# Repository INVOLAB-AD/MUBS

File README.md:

# MUBS_Drone_Design

It is the schematic design of the small microcontroller chip and of MUBS drones

The main components of the chip are:
1. ATTINY85U
2. MALE USB PORT
3. LEDS
4. RESISTORS
5. DIODES IN14007
6. PIN HEADERS

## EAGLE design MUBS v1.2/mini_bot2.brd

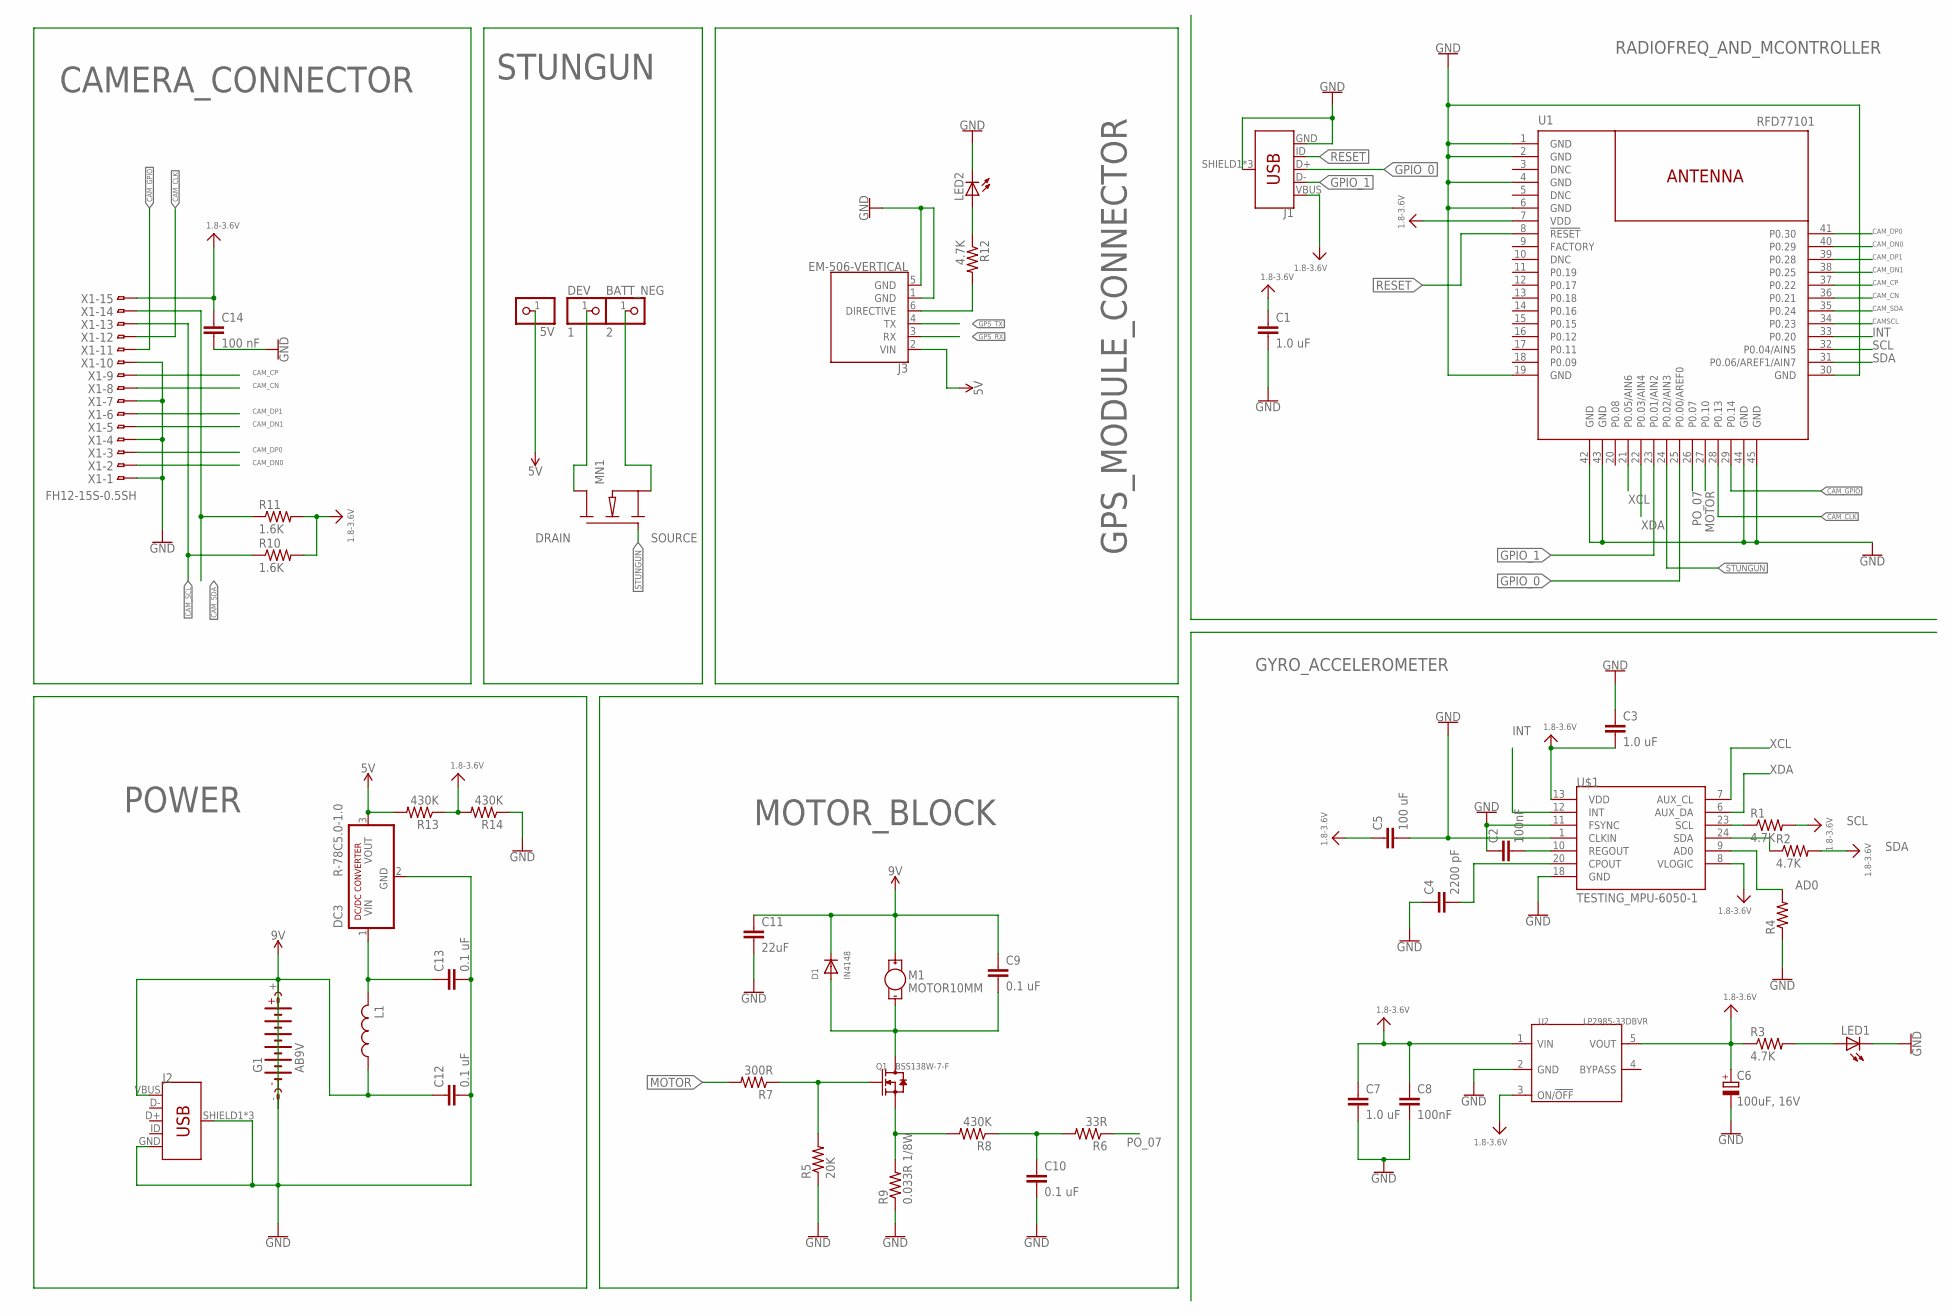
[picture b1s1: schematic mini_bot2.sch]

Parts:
5V: PINHD-1X1; 1X01
BATT_NEG: 2; 1X01
C1, C3, C7: 1.0 uF; C2.5-3
C2, C8: 100nF; C2.5-3
C4: 2200 pF; C2.5-3
C5: 100 uF; C2.5-3
C6: 100uF, 16V; A/3216-18R
C9, C10, C12, C13: 0.1 uF; C2.5-3
C11: 22uF; C2.5-3
C14: 100 nF; C2.5-3
D1: IN4148; DO-1N4148
DC3: R-78C5.0-1.0; SIP3
DEV: 1; 1X01
G1: AB9V
J1, J2: USB_MICRO-BREDUCED_PASTE; USB-B-MICRO-SMD_RED_PASTE
J3: EM-506-VERTICAL; JST-6PIN-1MM
L1: L-USL1812; L1812
LED1, LED2: LEDCHIPLED_1206; CHIPLED_1206
M1: MOTOR10MM; VIBE-MOTOR-10MM
MN1: NMOS; SOT23
Q1: BSS138W-7-F; SOT-23
R1, R2, R3, R12: 4.7K; M0805
R4: R-US_M0805; M0805
R5: 20K; M0805
R6: 33R; M0805
R7: 300R; M0805
R8, R13, R14: 430K; M0805
R9: 0.033R 1/8W; M0805
R10, R11: 1.6K; M0805
U1: RFD77101
U2: LP2985-33DBVR; SOT-23-5
U$1: TESTING_MPU-6050-1; TESTING_QFN-24-4MM2
X1: FH12-15S-0.5SH

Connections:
5V: 5V.1, DC3.3 (VOUT), J3.2 (VIN), R13.2
12V: C9.1, C11.1, C12.1, D1.C, G1.+, J2.VBUS, L1.1, M1.+
AD0: R4.2, U$1.9 (AD0)
CAMSCL: U1.34 (P0.23)
CAM_CLK: U1.28 (P0.13), X1.12
CAM_CN: U1.36 (P0.21), X1.8
CAM_CP: U1.37 (P0.22), X1.9
CAM_DN0: U1.40 (P0.29), X1.2
CAM_DN1: U1.38 (P0.25), X1.5
CAM_DP0: U1.41 (P0.30), X1.3
CAM_DP1: U1.39 (P0.28), X1.6
CAM_GPIO: U1.29 (P0.14), X1.11
CAM_SCL: R10.1, X1.13
CAM_SDA: R11.1, U1.35 (P0.24), X1.14
DRAIN: DEV.1, MN1.3 (D)
GND: C1.2, C2.1, C3.1, C4.1, C5.2, C6.-, C7.2, C8.2, C10.2, C11.2, C12.2, C13.2, C14.2, DC3.2 (GND), G1.-, J1.GND, J1.SHIELD1 (SHIELD), J1.SHIELD2 (SHIELD), J1.SHIELD3 (SHIELD), J2.GND, J2.SHIELD1 (SHIELD), J2.SHIELD2 (SHIELD), J2.SHIELD3 (SHIELD), J3.1 (GND), J3.5 (GND), LED1.C, LED2.C, R4.1, R5.1, R9.1, R14.1, U1.1 (GND), U1.2 (GND), U1.4 (GND), U1.6 (GND), U1.19 (GND), U1.30 (GND), U1.42 (GND), U1.43 (GND), U1.44 (GND), U1.45 (GND), U2.2 (GND), U$1.1 (CLKIN), U$1.11 (FSYNC), U$1.18 (GND), X1.1, X1.4, X1.7, X1.10
GPIO_0: J1.D+, U1.25 (P0.00/AREF0)
GPIO_1: J1.D-, U1.23 (P0.01/AIN2)
GPS_RX: J3.3 (RX)
GPS_TX: J3.4 (TX)
INT: U1.33 (P0.20), U$1.12 (INT)
MOTOR: R7.2, U1.27 (P0.10)
unnamed: C9.2, D1.A, M1.-, Q1.3 (D)
unnamed: LED1.A, R3.2
unnamed: C4.2, U$1.20 (CPOUT)
unnamed: C2.2, U$1.10 (REGOUT)
unnamed: C13.1, DC3.1 (VIN), L1.2
unnamed: Q1.2 (S), R8.2, R9.2
unnamed: C10.1, R6.2, R8.1
unnamed: Q1.1 (G), R5.2, R7.1
unnamed: J3.6 (DIRECTIVE), R12.2
unnamed: LED2.A, R12.1
PO_07: R6.1, U1.26 (P0.07)
RESET: J1.ID, U1.8 (!RESET!)
SCL: R1.1, U1.32 (P0.04/AIN5), U$1.23 (SCL)
SDA: R2.1, U1.31 (P0.06/AREF1/AIN7), U$1.24 (SDA)
SOURCE: BATT_NEG.1, MN1.2 (S)
STUNGUN: MN1.1 (G), U1.24 (P0.02/AIN3)
VCC: C1.1, C3.2, C5.1, C6.+, C7.1, C8.1, C14.1, J1.VBUS, R1.2, R2.2, R3.1, R10.2, R11.2, R13.1, R14.2, U1.7 (VDD), U2.1 (VIN), U2.3 (ON/!OFF), U2.5 (VOUT), U$1.8 (VLOGIC), U$1.13 (VDD), X1.15
XCL: U1.21 (P0.05/AIN6), U$1.7 (AUX_CL)
XDA: U1.22 (P0.03/AIN4), U$1.6 (AUX_DA)

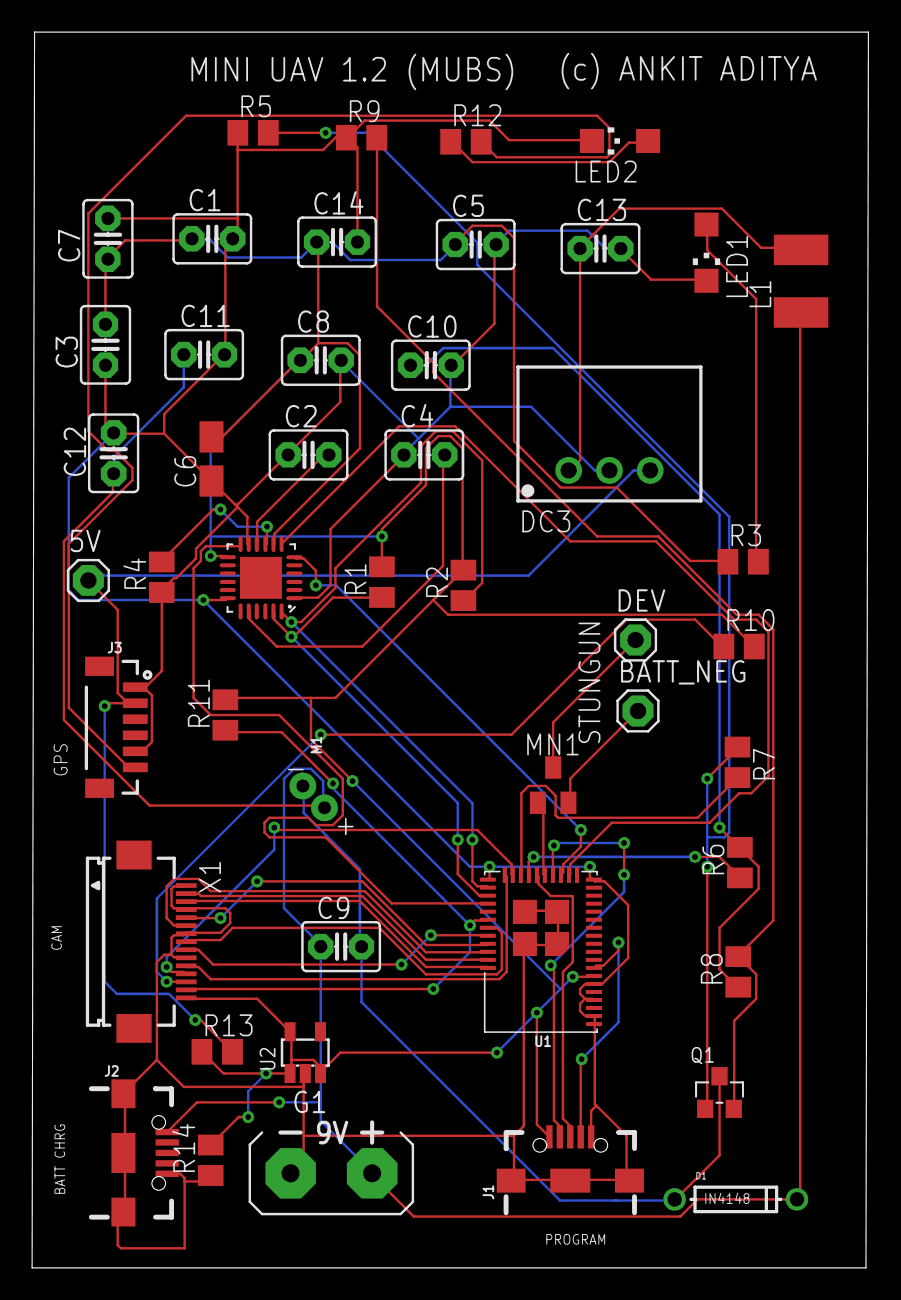
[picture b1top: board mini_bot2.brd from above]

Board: 2 copper layers, 52.1 x 77.0 mm, 47 parts (0 on the bottom side), 38 nets.

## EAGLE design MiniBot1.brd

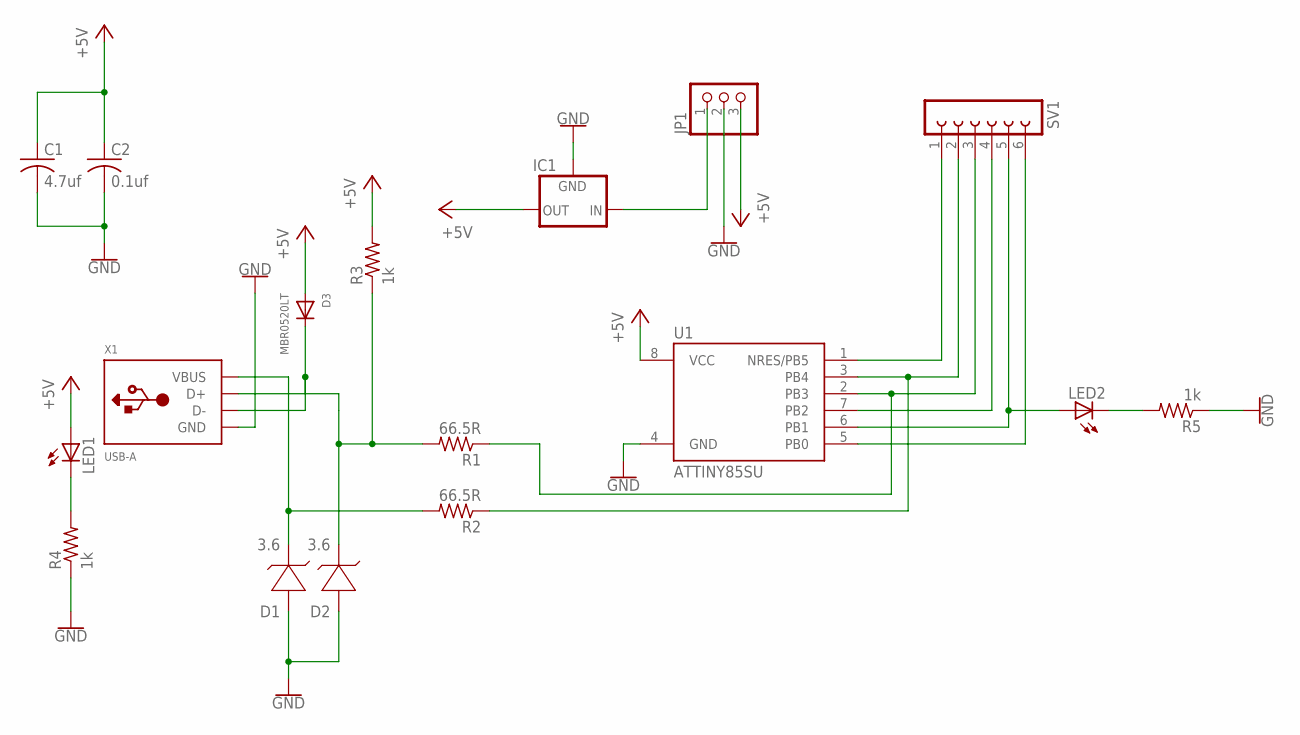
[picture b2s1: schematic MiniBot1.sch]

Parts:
C1: 4.7uf; C0402
C2: 0.1uf; C0402
D1, D2: 3.6; SOD123
D3: MBR0520LT; SOD-523
IC1: MCP1700INLINE; TO92-INLINE
JP1: PINHD-1X3; 1X03
LED1, LED2: LED; SMARTLED-TTW
R1, R2: 66.5R; M0805
R3, R4, R5: 1k; M0805
SV1: FE06-1; FE06
U1: ATTINY85SU; ATTINY85
X1: USB-A; MOLEX_480371000

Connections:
+5V: C1.1, C2.1, D3.A, IC1.3 (OUT), JP1.3, LED1.A@1 (A), R3.2, U1.8 (VCC)
GND: C1.2, C2.2, D1.A (+), D2.A (+), IC1.1 (GND), JP1.2, R4.1, R5.1, U1.4 (GND), X1.4 (GND)
unnamed: SV1.1, U1.1 (NRES/PB5)
unnamed: R2.1, SV1.2, U1.3 (PB4)
unnamed: R1.1, SV1.3, U1.2 (PB3)
unnamed: SV1.4, U1.7 (PB2)
unnamed: LED2.A@1 (A), SV1.5, U1.6 (PB1)
unnamed: SV1.6, U1.5 (PB0)
unnamed: D2.C (-), R1.2, R3.1, X1.3 (D+)
unnamed: D1.C (-), R2.2, X1.1 (VBUS)
unnamed: D3.K (C), X1.2 (D-)
unnamed: IC1.2 (IN), JP1.1
unnamed: LED1.C@1 (C), R4.2
unnamed: LED2.C@1 (C), R5.2

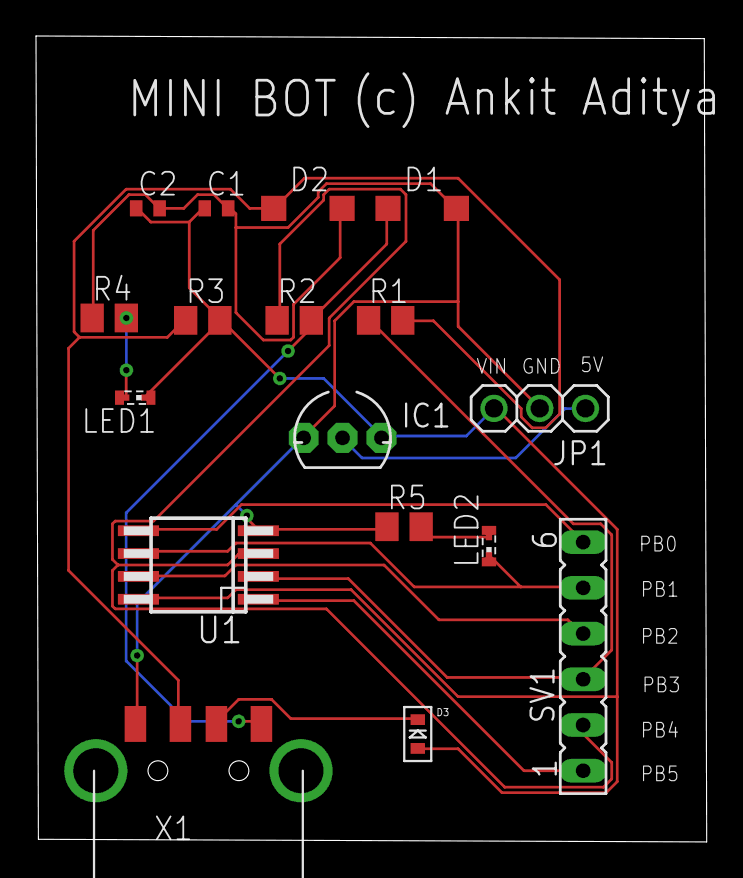
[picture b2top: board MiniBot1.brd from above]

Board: 2 copper layers, 37.3 x 44.8 mm, 17 parts (0 on the bottom side), 14 nets.

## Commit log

2018-09-27 First Phase Schematic design
2018-10-06 MUBS v1.1

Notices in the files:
parts and their libraries:
SparkFun-Connectors: Licensing: Creative Commons ShareAlike 4.0 International - https://creativecommons.org/licenses/by-sa/4.0
SparkFun-RF: © 2015 RF Digital Corporation
